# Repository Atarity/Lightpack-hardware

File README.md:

Lightpack-hardware
==================

Lightpack hardware schematics and layouts in CAD Eagle 6+ . This repo was started privately by reason of R&amp;D.

-------------------------
All updates stores in [CHANGELOG] (/Atarity/Lightpack-hardware/blob/master/CHANGELOG) file
* L &mdash; DIY versions
* T &mdash; mass-production preview versions

No GERBERs, no extension-hashed backups. All research and derivatives in branches.

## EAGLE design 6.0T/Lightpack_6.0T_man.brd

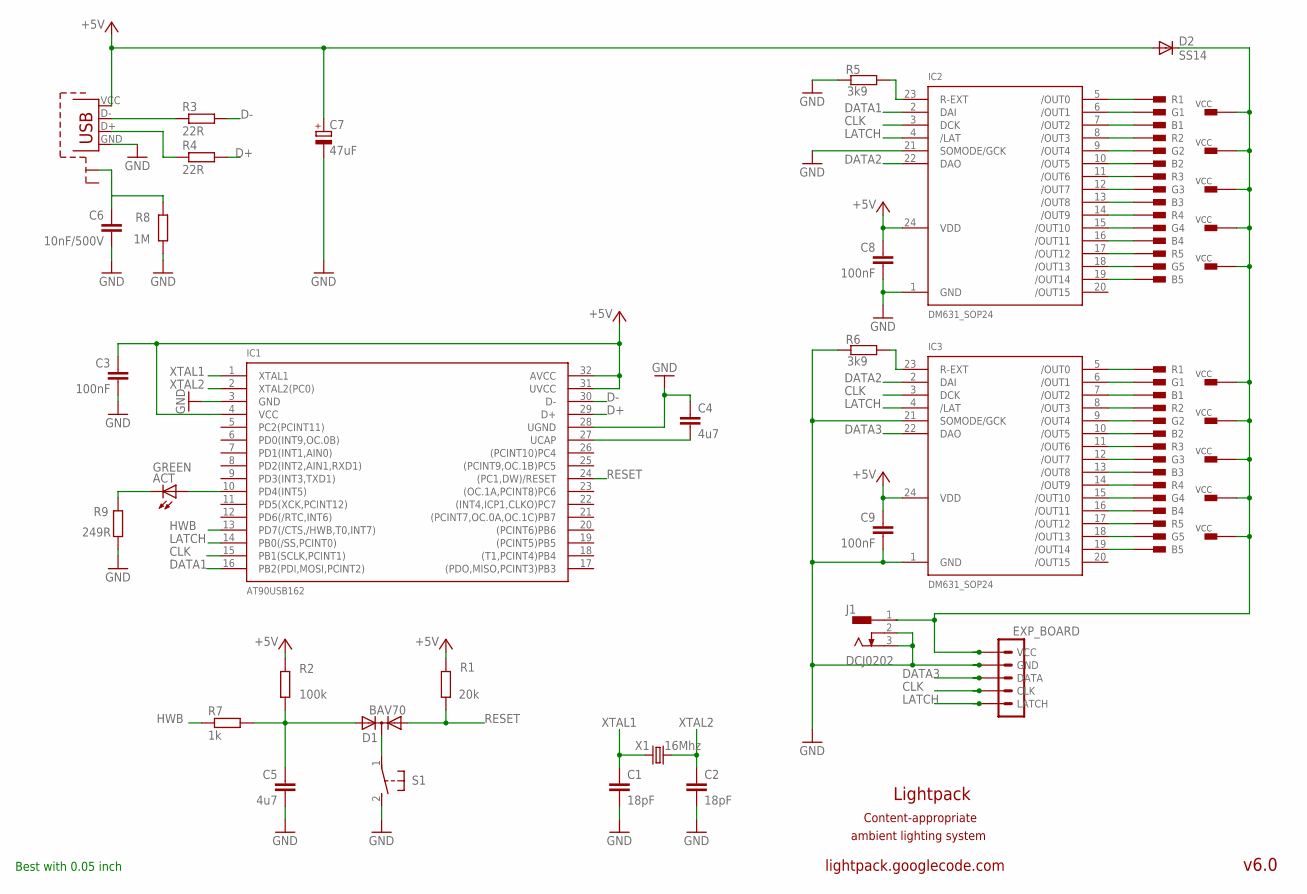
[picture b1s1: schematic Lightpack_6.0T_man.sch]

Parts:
ACT: GREEN; LED3MM
C1, C2: 18pF; C0805
C3, C8, C9: 100nF; C0805
C4, C5: 4u7; C0805
C6: 10nF/500V; C0805
C7: 47uF; SMC_D
CN1: USB-MICRO-B-EVT; USB-MICRO-B-UNIVERSAL-SOLID-FOOTS
CN2: RJ11-5P-REEL-LIGHTPACK6T2; RJ11-1XN-5P
CN3: RJ11-5P-REEL-MAIN; RJ11-1XN-5P
D1: BAV70; SOT23
D2: SS14; SMB
EXP_BOARD: MA05-1
IC1: AT90USB162; TQFP32
IC2, IC3: DM631_SOP24; SOP24-300-1.27
J1: DCJ0202
R1: 20k; R0805
R2: 100k; R0805
R3, R4: 22R; R0805
R5, R6: 3k9; R0805
R7: 1k; R0805
R8: 1M; R0805
R9: 249R; R0805
S1: 31-XX; B3F-31XX
X1: 16Mhz; HC49UP

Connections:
+5V: C3.1, C7.+, C8.1, C9.1, CN1.VCC (VBUS), D2.A, IC1.4 (VCC), IC1.31 (UVCC), IC1.32 (AVCC), IC2.24 (VDD), IC3.24 (VDD), R1.2, R2.2
CLK: EXP_BOARD.2 (CLK), IC1.15 (PB1(SCLK,PCINT1)), IC2.3 (DCK), IC3.3 (DCK)
D+: IC1.29 (D+), R4.2
D-: IC1.30 (D-), R3.2
DATA1: IC1.16 (PB2(PDI,MOSI,PCINT2)), IC2.2 (DAI)
DATA2: IC2.22 (DAO), IC3.2 (DAI)
DATA3: EXP_BOARD.3 (DATA), IC3.22 (DAO)
GND: C1.2, C2.2, C3.2, C4.1, C5.2, C6.1, C7.-, C8.2, C9.2, CN1.GND, EXP_BOARD.4 (GND), IC1.3 (GND), IC1.28 (UGND), IC2.1 (GND), IC2.21 (SOMODE/GCK), IC3.1 (GND), IC3.21 (SOMODE/GCK), J1.2, J1.3, R5.1, R6.1, R8.1, R9.1, S1.2 (S)
HWB: IC1.13 (PD7(/CTS,/HWB,T0,INT7)), R7.1
LATCH: EXP_BOARD.1 (LATCH), IC1.14 (PB0(/SS,PCINT0)), IC2.4 (/LAT), IC3.4 (/LAT)
unnamed: IC2.23 (R-EXT), R5.2
unnamed: CN3.R2, IC3.8 (/OUT3)
unnamed: ACT.A, IC1.10 (PD4(INT5))
unnamed: CN2.R5 (R1), IC2.5 (/OUT0)
unnamed: CN2.G5 (G1), IC2.6 (/OUT1)
unnamed: CN2.B5 (B1), IC2.7 (/OUT2)
unnamed: CN2.R4 (R2), IC2.8 (/OUT3)
unnamed: CN2.G4 (G2), IC2.9 (/OUT4)
unnamed: CN2.B4 (B2), IC2.10 (/OUT5)
unnamed: CN2.R1 (R3), IC2.11 (/OUT6)
unnamed: CN2.G1 (G3), IC2.12 (/OUT7)
unnamed: CN2.B1 (B3), IC2.13 (/OUT8)
unnamed: CN2.R2 (R4), IC2.14 (/OUT9)
unnamed: D1.3 (C), S1.1
unnamed: C4.2, IC1.27 (UCAP)
unnamed: CN3.R1, IC3.5 (/OUT0)
unnamed: CN3.G1, IC3.6 (/OUT1)
unnamed: CN3.B1, IC3.7 (/OUT2)
unnamed: CN3.G2, IC3.9 (/OUT4)
unnamed: CN3.B2, IC3.10 (/OUT5)
unnamed: CN3.R3, IC3.11 (/OUT6)
unnamed: CN3.G3, IC3.12 (/OUT7)
unnamed: CN3.R4, IC3.14 (/OUT9)
unnamed: CN3.B3, IC3.13 (/OUT8)
unnamed: CN3.G4, IC3.15 (/OUT10)
unnamed: CN3.B4, IC3.16 (/OUT11)
unnamed: CN2.G2 (G4), IC2.15 (/OUT10)
unnamed: CN2.B2 (B4), IC2.16 (/OUT11)
unnamed: IC3.23 (R-EXT), R6.2
unnamed: CN1.D-, R3.1
unnamed: CN1.D+, R4.1
unnamed: ACT.K (C), R9.2
unnamed: CN2.R3 (R5), IC2.17 (/OUT12)
unnamed: CN2.G3 (G5), IC2.18 (/OUT13)
unnamed: CN2.B3 (B5), IC2.19 (/OUT14)
unnamed: CN3.R5, IC3.17 (/OUT12)
unnamed: CN3.G5, IC3.18 (/OUT13)
unnamed: CN3.B5, IC3.19 (/OUT14)
unnamed: C6.2, CN1.P$4 (SHIELD1), R8.2
unnamed: C5.1, D1.2 (A2), R2.1, R7.2
unnamed: CN2.VCC1 (VCC3), CN2.VCC2 (VCC4), CN2.VCC3 (VCC5), CN2.VCC4 (VCC2), CN2.VCC5 (VCC1), CN3.VCC1, CN3.VCC2, CN3.VCC3, CN3.VCC4, CN3.VCC5, D2.C, EXP_BOARD.5 (VCC), J1.1
RESET: D1.1 (A1), IC1.24 ((PC1,DW)/RESET), R1.1
XTAL1: C1.1, IC1.1 (XTAL1), X1.1
XTAL2: C2.1, IC1.2 (XTAL2(PC0)), X1.2

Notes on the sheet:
lightpack.googlecode.com
Lightpack
ambient lighting system
v6.0
Content-appropriate
Best with 0.05 inch

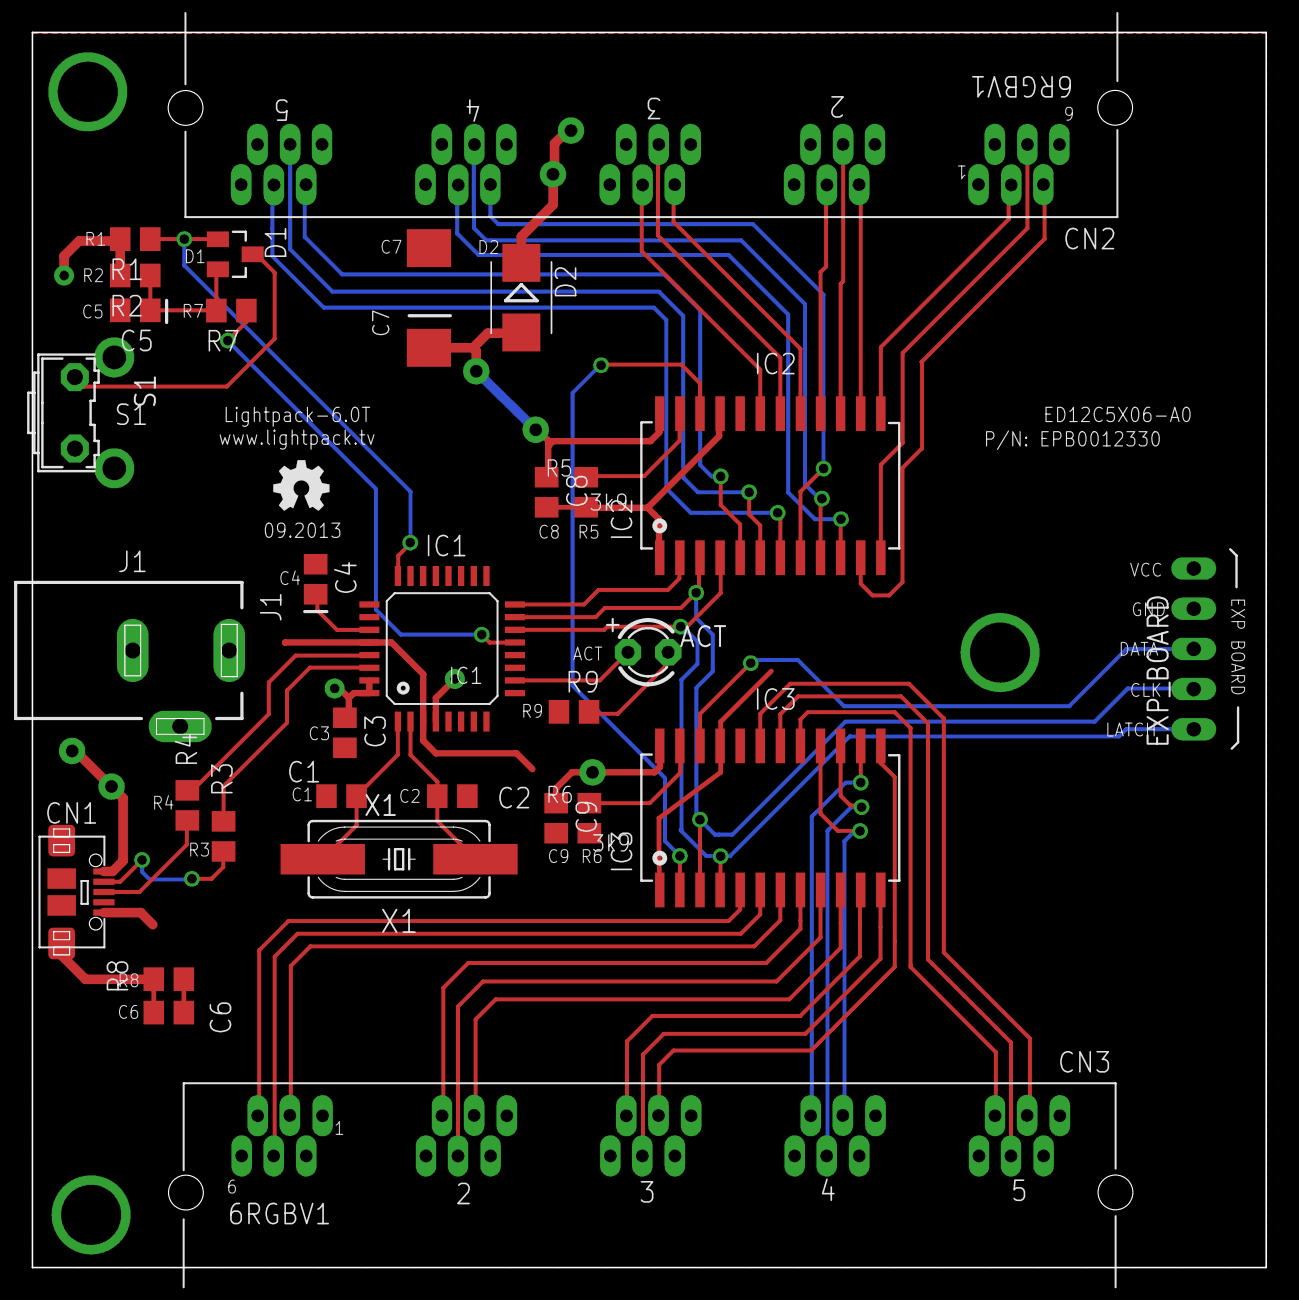
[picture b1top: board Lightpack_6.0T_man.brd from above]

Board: 2 copper layers, 78.0 x 78.1 mm, 31 parts (0 on the bottom side), 54 nets.

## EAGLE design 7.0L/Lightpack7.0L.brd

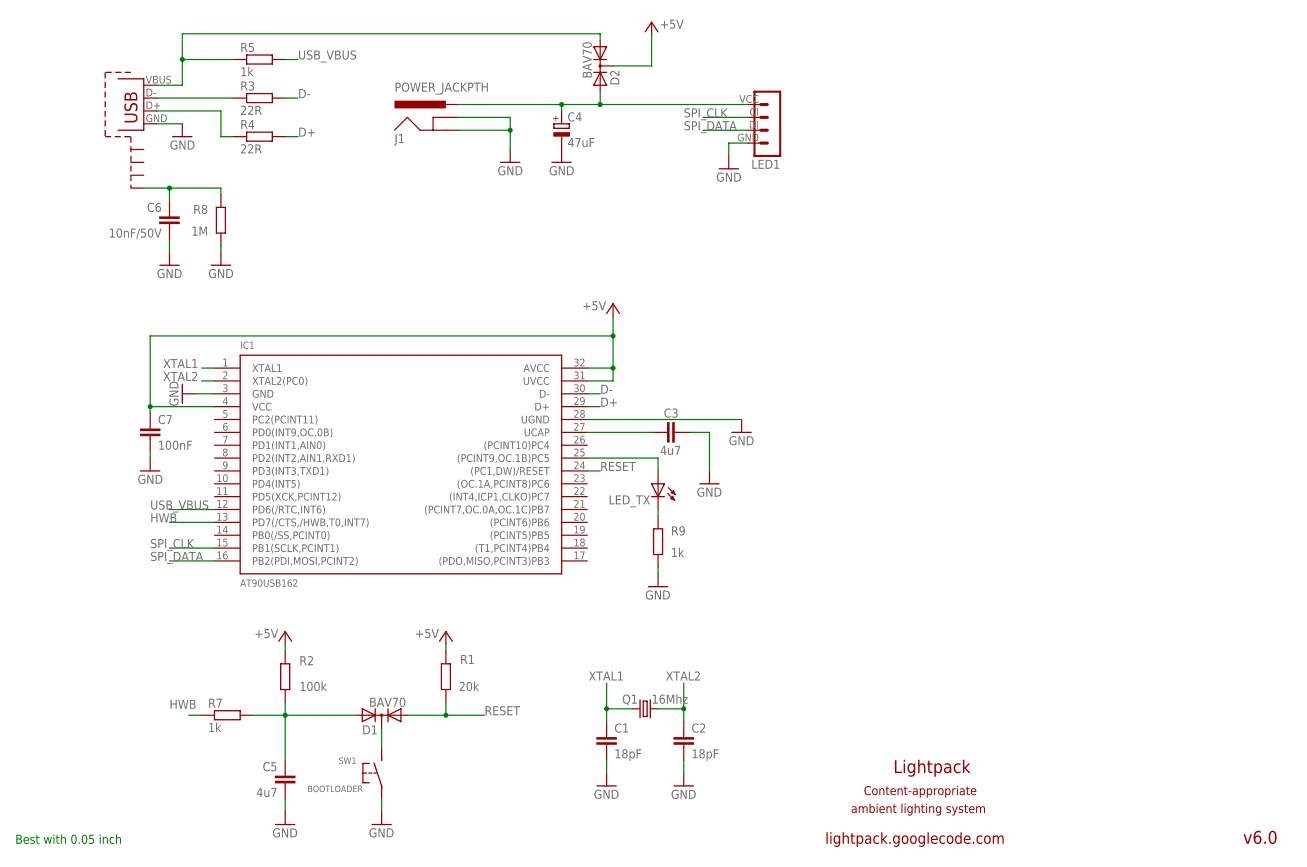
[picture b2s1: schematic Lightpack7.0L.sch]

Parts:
C1, C2: 18pF; C1206
C3, C5: 4u7; C1206
C4: 47uF; D/7343-31W
C6: 10nF/50V; C1206
C7: 100nF; C1206
D1, D2: BAV70; SOT23
IC1: AT90USB162; TQFP32
J1: POWER_JACKPTH; POWER_JACK_PTH
LED1: RGB_LED_STRIP; MA04-1
LED_TX: GREEN; CHIPLED_0805
Q1: 16Mhz; HC49UP
R1: 20k; R1206
R2: 100k; R1206
R3, R4: 22R; R1206
R5, R7, R9: 1k; R1206
R8: 1M; R1206
SW1: BOOTLOADER; BUTTON-SMD
X1: USB-MB-S

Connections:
+5V: C7.1, IC1.4 (VCC), IC1.31 (UVCC), IC1.32 (AVCC), R1.2, R2.1 (2)
D+: IC1.29 (D+), R4.2
D-: IC1.30 (D-), R3.2
GND: C1.2, C2.2, C3.1, C4.-, C5.2, C6.2, C7.2, IC1.3 (GND), IC1.28 (UGND), J1.GND, J1.GNDBREAK, LED1.GND, R8.1, R9.1, SW1.1, X1.GND
HWB: IC1.13 (PD7(/CTS,/HWB,T0,INT7)), R7.1
unnamed: R4.1, X1.D+
unnamed: D2.1 (A1), R5.1, X1.VBUS
unnamed: R3.1, X1.D-
unnamed: C4.+, D2.2 (A2), J1.PWR, LED1.VCC
unnamed: IC1.25 ((PCINT9,OC.1B)PC5), LED_TX.A
unnamed: C6.1, R8.2, X1.SHIELD4
unnamed: LED_TX.C, R9.2
unnamed: D1.3 (C), SW1.2
unnamed: C5.1, D1.2 (A2), R2.2 (1), R7.2
unnamed: C3.2, IC1.27 (UCAP)
RESET: D1.1 (A1), IC1.24 ((PC1,DW)/RESET), R1.1
SPI_CLK: IC1.15 (PB1(SCLK,PCINT1)), LED1.CI
SPI_DATA: IC1.16 (PB2(PDI,MOSI,PCINT2)), LED1.DI
USB_VBUS: IC1.12 (PD6(/RTC,INT6)), R5.2
XTAL1: C1.1, IC1.1 (XTAL1), Q1.1
XTAL2: C2.1, IC1.2 (XTAL2(PC0)), Q1.2

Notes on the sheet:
lightpack.googlecode.com
Lightpack
ambient lighting system
v6.0
Content-appropriate
Best with 0.05 inch

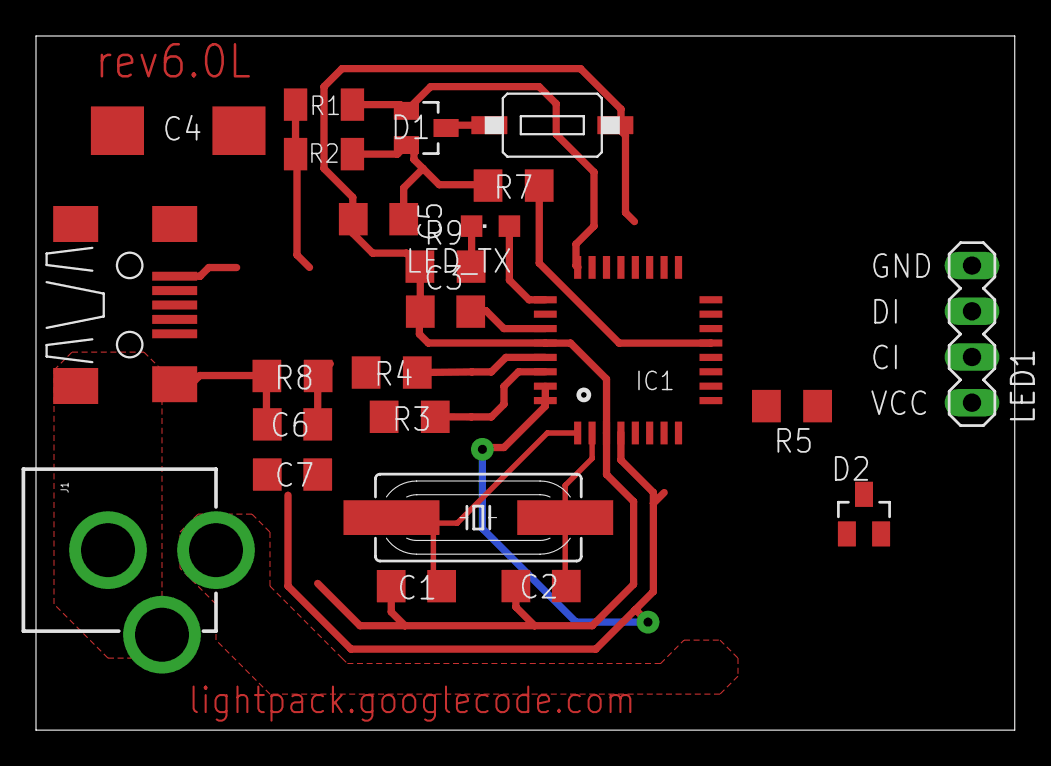
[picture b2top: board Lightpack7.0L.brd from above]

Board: 2 copper layers, 54.4 x 38.6 mm, 24 parts (0 on the bottom side), 21 nets.

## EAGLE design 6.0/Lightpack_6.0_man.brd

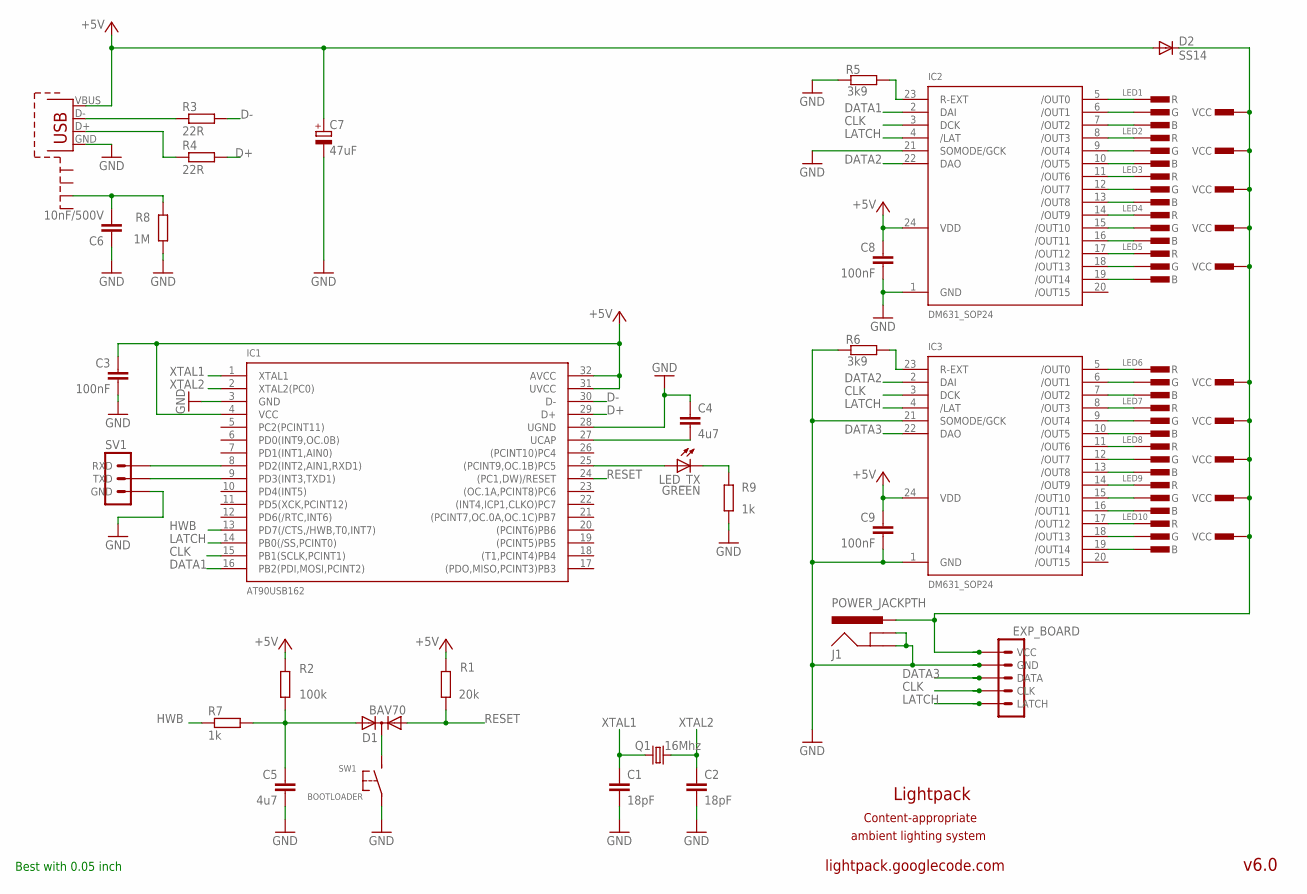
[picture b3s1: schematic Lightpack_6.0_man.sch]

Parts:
C1, C2: 18pF; C0805
C3, C8, C9: 100nF; C0805
C4, C5: 4u7; C0805
C6: 10nF/500V; C0805
C7: 47uF; SMC_D
D1: BAV70; SOT23
D2: SS14; SMB
EXP_BOARD: MA05-1
IC1: AT90USB162; TQFP32
IC2, IC3: DM631_SOP24; SOP24-300-1.27
J1: POWER_JACKPTH; POWER_JACK_PTH
LED1, LED2, LED3, LED4, LED5, LED6, LED7, LED8, LED9, LED10: CON-RGB-LED; CON-RGB-LED-TH
LED_TX: GREEN; CHIPLED_0805
Q1: 16Mhz; HC49UP
R1: 20k; R0805
R2: 100k; R0805
R3, R4: 22R; R0805
R5, R6: 3k9; R0805
R7, R9: 1k; R0805
R8: 1M; R0805
SV1: UART3
SW1: BOOTLOADER; BUTTON-SMD
X1: USB-MB-S

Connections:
+5V: C3.1, C7.+, C8.1, C9.1, D2.A, IC1.4 (VCC), IC1.31 (UVCC), IC1.32 (AVCC), IC2.24 (VDD), IC3.24 (VDD), R1.2, R2.2, X1.VBUS
CLK: EXP_BOARD.2 (CLK), IC1.15 (PB1(SCLK,PCINT1)), IC2.3 (DCK), IC3.3 (DCK)
D+: IC1.29 (D+), R4.2
D-: IC1.30 (D-), R3.2
DATA1: IC1.16 (PB2(PDI,MOSI,PCINT2)), IC2.2 (DAI)
DATA2: IC2.22 (DAO), IC3.2 (DAI)
DATA3: EXP_BOARD.3 (DATA), IC3.22 (DAO)
GND: C1.2, C2.2, C3.2, C4.1, C5.2, C6.1, C7.-, C8.2, C9.2, EXP_BOARD.4 (GND), IC1.3 (GND), IC1.28 (UGND), IC2.1 (GND), IC2.21 (SOMODE/GCK), IC3.1 (GND), IC3.21 (SOMODE/GCK), J1.GND, J1.GNDBREAK, R5.1, R6.1, R8.1, R9.1, SV1.1-L (GND), SW1.1, X1.GND
HWB: IC1.13 (PD7(/CTS,/HWB,T0,INT7)), R7.1
LATCH: EXP_BOARD.1 (LATCH), IC1.14 (PB0(/SS,PCINT0)), IC2.4 (/LAT), IC3.4 (/LAT)
unnamed: IC2.23 (R-EXT), R5.2
unnamed: IC3.8 (/OUT3), LED7.3.R (R)
unnamed: IC1.8 (PD2(INT2,AIN1,RXD1)), SV1.2 (RXD)
unnamed: IC1.9 (PD3(INT3,TXD1)), SV1.3-R (TXD)
unnamed: IC2.5 (/OUT0), LED1.3.R (R)
unnamed: IC2.6 (/OUT1), LED1.2.G (G)
unnamed: IC2.7 (/OUT2), LED1.1.B (B)
unnamed: IC1.25 ((PCINT9,OC.1B)PC5), LED_TX.A
unnamed: IC2.8 (/OUT3), LED2.3.R (R)
unnamed: IC2.9 (/OUT4), LED2.2.G (G)
unnamed: IC2.10 (/OUT5), LED2.1.B (B)
unnamed: IC2.11 (/OUT6), LED3.3.R (R)
unnamed: IC2.12 (/OUT7), LED3.2.G (G)
unnamed: IC2.13 (/OUT8), LED3.1.B (B)
unnamed: IC2.14 (/OUT9), LED4.3.R (R)
unnamed: C4.2, IC1.27 (UCAP)
unnamed: IC3.5 (/OUT0), LED6.3.R (R)
unnamed: IC3.6 (/OUT1), LED6.2.G (G)
unnamed: IC3.7 (/OUT2), LED6.1.B (B)
unnamed: IC3.9 (/OUT4), LED7.2.G (G)
unnamed: IC3.10 (/OUT5), LED7.1.B (B)
unnamed: IC3.11 (/OUT6), LED8.3.R (R)
unnamed: IC3.12 (/OUT7), LED8.2.G (G)
unnamed: IC3.14 (/OUT9), LED9.3.R (R)
unnamed: IC3.13 (/OUT8), LED8.1.B (B)
unnamed: IC3.15 (/OUT10), LED9.2.G (G)
unnamed: IC3.16 (/OUT11), LED9.1.B (B)
unnamed: IC2.15 (/OUT10), LED4.2.G (G)
unnamed: IC2.16 (/OUT11), LED4.1.B (B)
unnamed: IC3.23 (R-EXT), R6.2
unnamed: R3.1, X1.D-
unnamed: R4.1, X1.D+
unnamed: LED_TX.C, R9.2
unnamed: IC2.17 (/OUT12), LED5.3.R (R)
unnamed: IC2.18 (/OUT13), LED5.2.G (G)
unnamed: IC2.19 (/OUT14), LED5.1.B (B)
unnamed: IC3.17 (/OUT12), LED10.3.R (R)
unnamed: IC3.18 (/OUT13), LED10.2.G (G)
unnamed: IC3.19 (/OUT14), LED10.1.B (B)
unnamed: C6.2, R8.2, X1.SHIELD3
unnamed: D1.3 (C), SW1.2
unnamed: C5.1, D1.2 (A2), R2.1, R7.2
unnamed: D2.C, EXP_BOARD.5 (VCC), J1.PWR, LED1.4.VCC (VCC), LED2.4.VCC (VCC), LED3.4.VCC (VCC), LED4.4.VCC (VCC), LED5.4.VCC (VCC), LED6.4.VCC (VCC), LED7.4.VCC (VCC), LED8.4.VCC (VCC), LED9.4.VCC (VCC), LED10.4.VCC (VCC)
RESET: D1.1 (A1), IC1.24 ((PC1,DW)/RESET), R1.1
XTAL1: C1.1, IC1.1 (XTAL1), Q1.1
XTAL2: C2.1, IC1.2 (XTAL2(PC0)), Q1.2

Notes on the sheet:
lightpack.googlecode.com
Lightpack
ambient lighting system
v6.0
Content-appropriate
Best with 0.05 inch

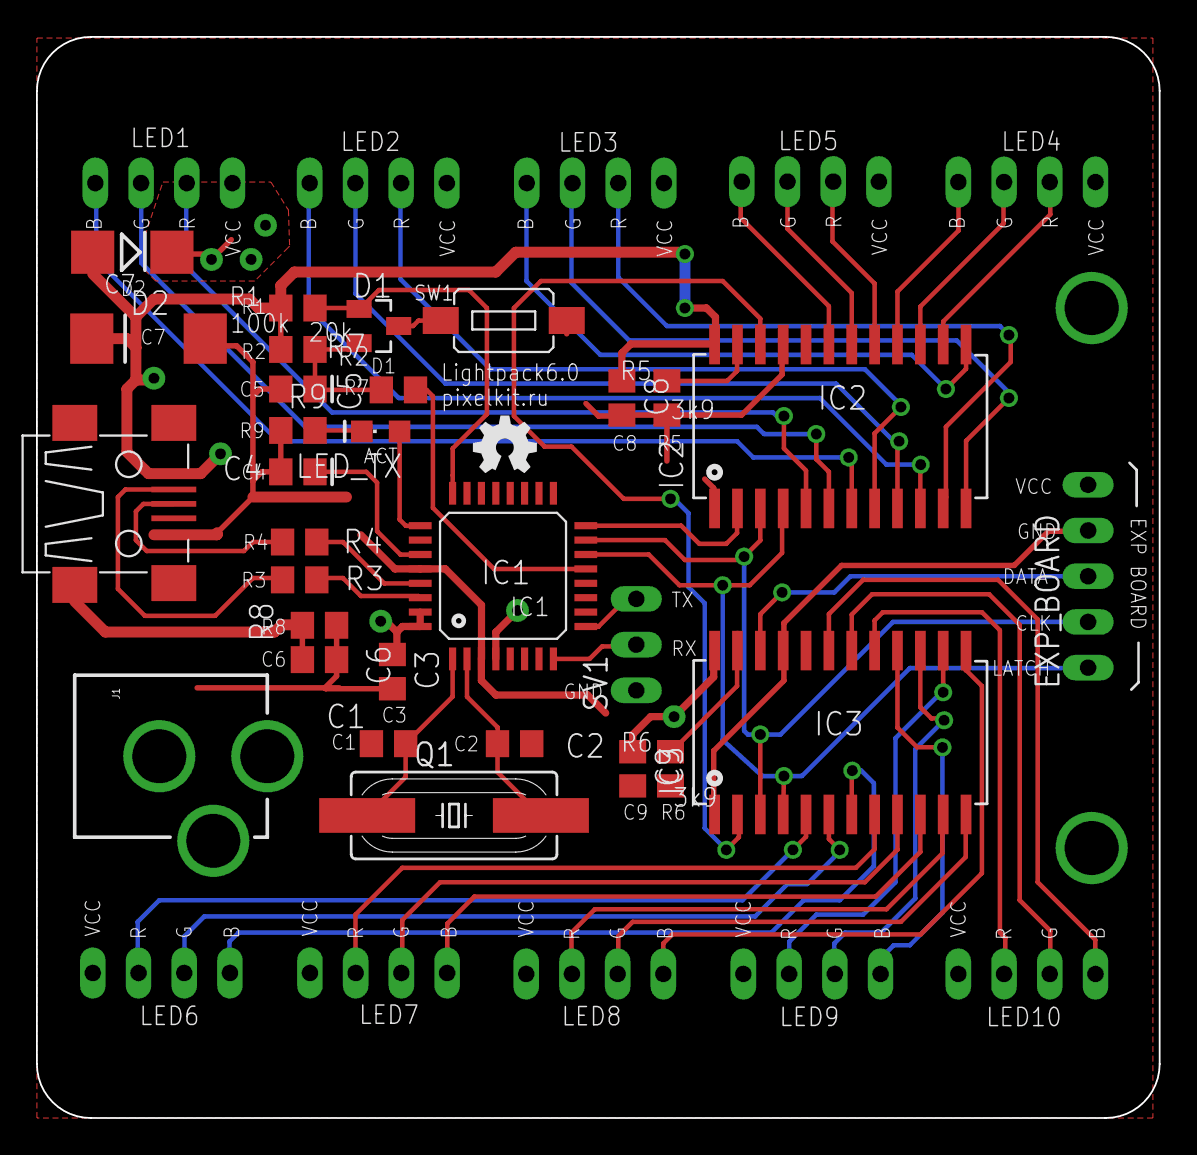
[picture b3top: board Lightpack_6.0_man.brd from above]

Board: 2 copper layers, 62.4 x 60.1 mm, 40 parts (0 on the bottom side), 56 nets.

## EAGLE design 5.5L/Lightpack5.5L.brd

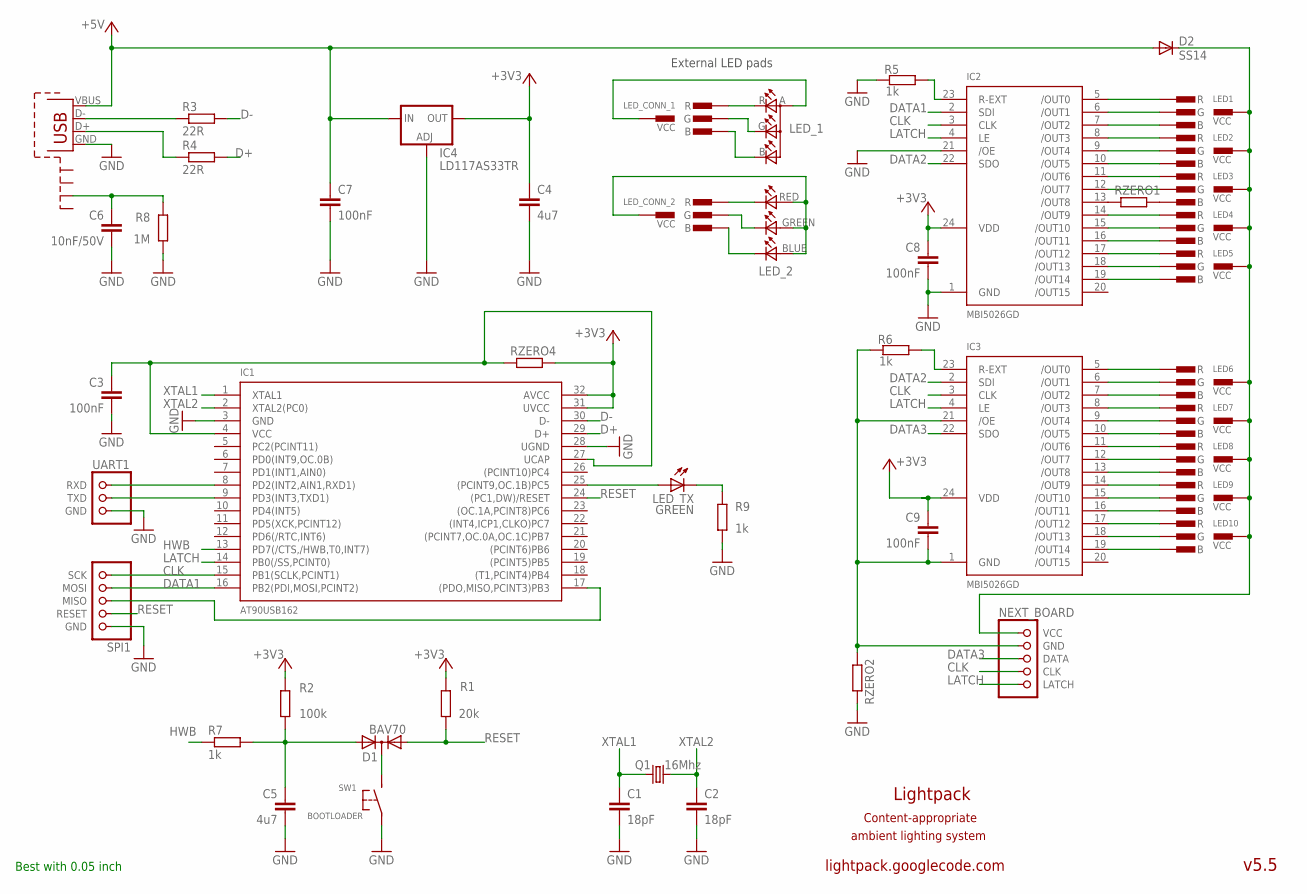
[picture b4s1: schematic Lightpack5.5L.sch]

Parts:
C1, C2: 18pF; C1206
C3, C7, C8, C9: 100nF; C1206
C4, C5: 4u7; C1206
C6: 10nF/50V; C1206
D1: BAV70; SOT23
D2: SS14; SMB
IC1: AT90USB162; TQFP32
IC2, IC3: MBI5026GD; SOP24-300-1.27
IC4: LD117AS33TR; SOT223
LED1, LED2, LED3, LED6, LED7, LED8, LED9, LED10: CON-RGB-LED
LED4, LED5: CON-RGB-LEDVCC-INDENT; CON-RGB-LED-WITH-VCC-INDENT
LED_1: CLV1A-FKB
LED_2: TOPLED-3SMD5X5; SMD-RGB-5X5
LED_CONN_1, LED_CONN_2: CON-RGB-LED
LED_TX: GREEN; CHIPLED_0805
NEXT_BOARD: LED_DRIVER_BOARD; DATA-CLK-LATCH
Q1: 16Mhz; HC49UP
R1: 20k; R1206
R2: 100k; R1206
R3, R4: 22R; R1206
R5, R6, R7, R9: 1k; R1206
R8: 1M; R1206
RZERO1, RZERO4: R-EU_R1206_2; R1206
RZERO2: 0; R1206
SPI1: SPI_RST_GND_CONN; SPI_5
SW1: BOOTLOADER; BUTTON-SMD
UART1: UART
X1: USB-MB-S

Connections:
+3V3: C4.1, C8.1, C9.1, IC1.31 (UVCC), IC1.32 (AVCC), IC2.24 (VDD), IC3.24 (VDD), IC4.4 (OUT), R1.2, R2.1 (2), RZERO4.1 (2)
+5V: C7.1, D2.A, IC4.3 (IN), X1.VBUS
CLK: IC1.15 (PB1(SCLK,PCINT1)), IC2.3 (CLK), IC3.3 (CLK), NEXT_BOARD.CLK, SPI1.SCK
D+: IC1.29 (D+), R4.2
D-: IC1.30 (D-), R3.2
DATA1: IC1.16 (PB2(PDI,MOSI,PCINT2)), IC2.2 (SDI), SPI1.MOSI
DATA2: IC2.22 (SDO), IC3.2 (SDI)
DATA3: IC3.22 (SDO), NEXT_BOARD.DATA
GND: C1.2, C2.2, C3.2, C4.2, C5.2, C6.2, C7.2, C8.2, IC1.3 (GND), IC1.28 (UGND), IC2.1 (GND), IC2.21 (/OE), IC4.1 (ADJ), R5.1, R8.1, R9.1, RZERO2.1 (2), SPI1.GND, SW1.1, UART1.GND, X1.GND
HWB: IC1.13 (PD7(/CTS,/HWB,T0,INT7)), R7.1
LATCH: IC1.14 (PB0(/SS,PCINT0)), IC2.4 (LE), IC3.4 (LE), NEXT_BOARD.LATCH
unnamed: IC2.23 (R-EXT), R5.2
unnamed: IC3.8 (/OUT3), LED7.R
unnamed: IC1.17 ((PDO,MISO,PCINT3)PB3), SPI1.MISO
unnamed: IC1.8 (PD2(INT2,AIN1,RXD1)), UART1.RXD
unnamed: IC2.5 (/OUT0), LED1.R
unnamed: IC2.6 (/OUT1), LED1.G
unnamed: IC2.7 (/OUT2), LED1.B
unnamed: IC1.25 ((PCINT9,OC.1B)PC5), LED_TX.A
unnamed: IC2.8 (/OUT3), LED2.R
unnamed: IC2.9 (/OUT4), LED2.G
unnamed: IC2.10 (/OUT5), LED2.B
unnamed: IC2.11 (/OUT6), LED3.R
unnamed: IC2.12 (/OUT7), LED3.G
unnamed: IC2.13 (/OUT8), RZERO1.2 (1)
unnamed: IC2.14 (/OUT9), LED4.R
unnamed: IC1.9 (PD3(INT3,TXD1)), UART1.TXD
unnamed: LED_1.R (CRED), LED_CONN_1.R
unnamed: IC3.5 (/OUT0), LED6.R
unnamed: IC3.6 (/OUT1), LED6.G
unnamed: IC3.7 (/OUT2), LED6.B
unnamed: IC3.9 (/OUT4), LED7.G
unnamed: IC3.10 (/OUT5), LED7.B
unnamed: IC3.11 (/OUT6), LED8.R
unnamed: IC3.12 (/OUT7), LED8.G
unnamed: IC3.14 (/OUT9), LED9.R
unnamed: IC3.13 (/OUT8), LED8.B
unnamed: IC3.15 (/OUT10), LED9.G
unnamed: IC3.16 (/OUT11), LED9.B
unnamed: IC2.15 (/OUT10), LED4.G
unnamed: IC2.16 (/OUT11), LED4.B
unnamed: IC3.23 (R-EXT), R6.2
unnamed: R3.1, X1.D-
unnamed: R4.1, X1.D+
unnamed: LED_1.G (CGREEN), LED_CONN_1.G
unnamed: LED_1.B (CBLUE), LED_CONN_1.B
unnamed: LED_1.A (ANODE), LED_CONN_1.VCC
unnamed: LED_TX.C, R9.2
unnamed: IC2.17 (/OUT12), LED5.R
unnamed: IC2.18 (/OUT13), LED5.G
unnamed: IC2.19 (/OUT14), LED5.B
unnamed: IC3.17 (/OUT12), LED10.R
unnamed: IC3.18 (/OUT13), LED10.G
unnamed: IC3.19 (/OUT14), LED10.B
unnamed: C6.1, R8.2, X1.SHIELD3
unnamed: D1.3 (C), SW1.2
unnamed: C5.1, D1.2 (A2), R2.2 (1), R7.2
unnamed: C9.2, IC3.1 (GND), IC3.21 (/OE), NEXT_BOARD.GND, R6.1, RZERO2.2 (1)
unnamed: LED3.B, RZERO1.1 (2)
unnamed: LED_2.CRED, LED_CONN_2.R
unnamed: LED_2.CGREEN, LED_CONN_2.G
unnamed: LED_2.CBLUE, LED_CONN_2.B
unnamed: C3.1, IC1.4 (VCC), IC1.27 (UCAP), RZERO4.2 (1)
unnamed: LED_2.BLUE, LED_2.GREEN, LED_2.RED, LED_CONN_2.VCC
unnamed: D2.C, LED1.VCC, LED2.VCC, LED3.VCC, LED4.VCC, LED5.VCC, LED6.VCC, LED7.VCC, LED8.VCC, LED9.VCC, LED10.VCC, NEXT_BOARD.VCC
RESET: D1.1 (A1), IC1.24 ((PC1,DW)/RESET), R1.1, SPI1.RESET
XTAL1: C1.1, IC1.1 (XTAL1), Q1.1
XTAL2: C2.1, IC1.2 (XTAL2(PC0)), Q1.2

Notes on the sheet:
lightpack.googlecode.com
Lightpack
ambient lighting system
v5.5
Content-appropriate
External LED pads
Best with 0.05 inch

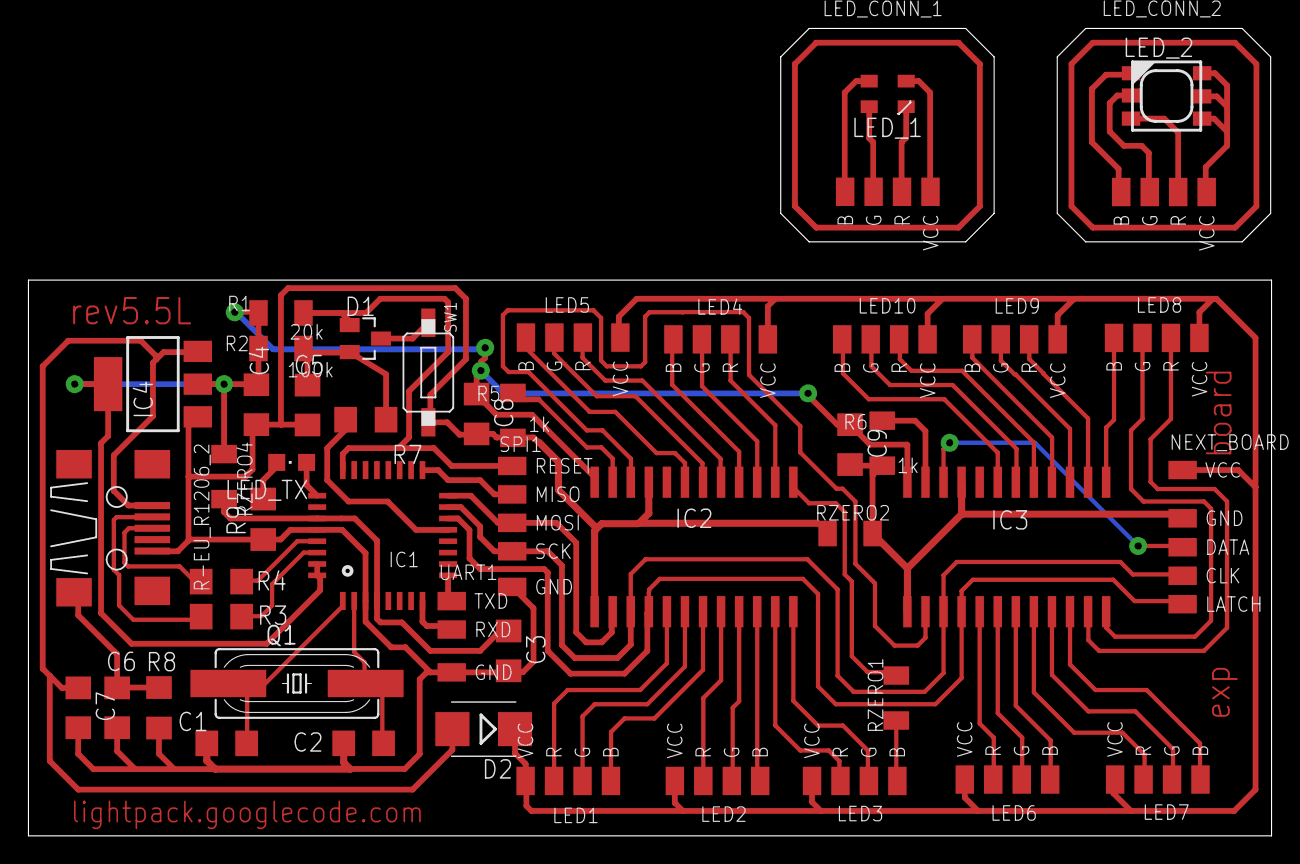
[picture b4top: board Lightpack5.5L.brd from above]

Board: 2 copper layers, 87.4 x 56.8 mm, 48 parts (0 on the bottom side), 68 nets.

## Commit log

2012-09-15 Initial tree commit, all in Eagle 6+
    * 5.5, 5.5L, 5.6, 6.0, 6.0L, 6.0T schematic and layouts
    * gitignor
    * CHANGELOG actualized
2012-09-15 Update CHANGELOG
2012-09-16 Front-line I/O rearranged
    * Button --> DJK02A --> microUSB
    * Expand PCB size for Alex case
    * Bottom polygons shape changes
2012-09-17 60T improved for casing
    * PCB size 76x71mm now
    * UART deletted
    * ACT LED now on pin 10 instead 25 (need to modify firmware)
    * ACT LED thru-hole d3 now (need to test R9)
    * 3 mount holes d3 od5
    * Significanty alot of space between components
2012-09-28 Top restriction added, minor changes on bottom.
    *GERBERS ignored in .gitignore
2012-10-02 I/O names for tPlace added and rearranged.
2012-10-04 Extended 78x78 version
    *Mount holes fixed
    *Dimensions fixed
    *Polylines fixed
2012-10-08 microUSB footprint adjust for pointer welding
2012-10-09 New universal microUSB footprint
    *Some restriction added
    *7 holes on milling (46) layer
2012-10-10 Basic Lightpack 7 schematics
    Support power from PSU and USB (split by diode BAV70).
    Added resistor (1k) for determine USB-power status.
2012-10-18 Fix names and R9 value
2013-07-22 Draft-angle enclosure type optimization
    * tPlace silk updated (url, year)
    * CN2, CN3 moved toward PCB center for 1mm
2013-08-02 tSilk + new microUSB socket + CN2,CN3 moving (see details)
    -- P/N + ID on tSilk
    -- Slots of mUSB increased to 1.0x0.5mm
    -- New solid rect in mUSB component (commited in Pixelkit lib) named EVT
    -- CN2,3 moved on 0.1mm out of center
2013-08-06 update microUSB foots for EVT (see EAGLE-libs commit)
2013-08-31 LED, RJ11 reel, Soldermask
    — Indicator LED shifted to the exp board on 1.3 mm
    — RJ11 reel pads with increased drill diameter
    — All vias up to 0.6 diameters now covers with soldermask
